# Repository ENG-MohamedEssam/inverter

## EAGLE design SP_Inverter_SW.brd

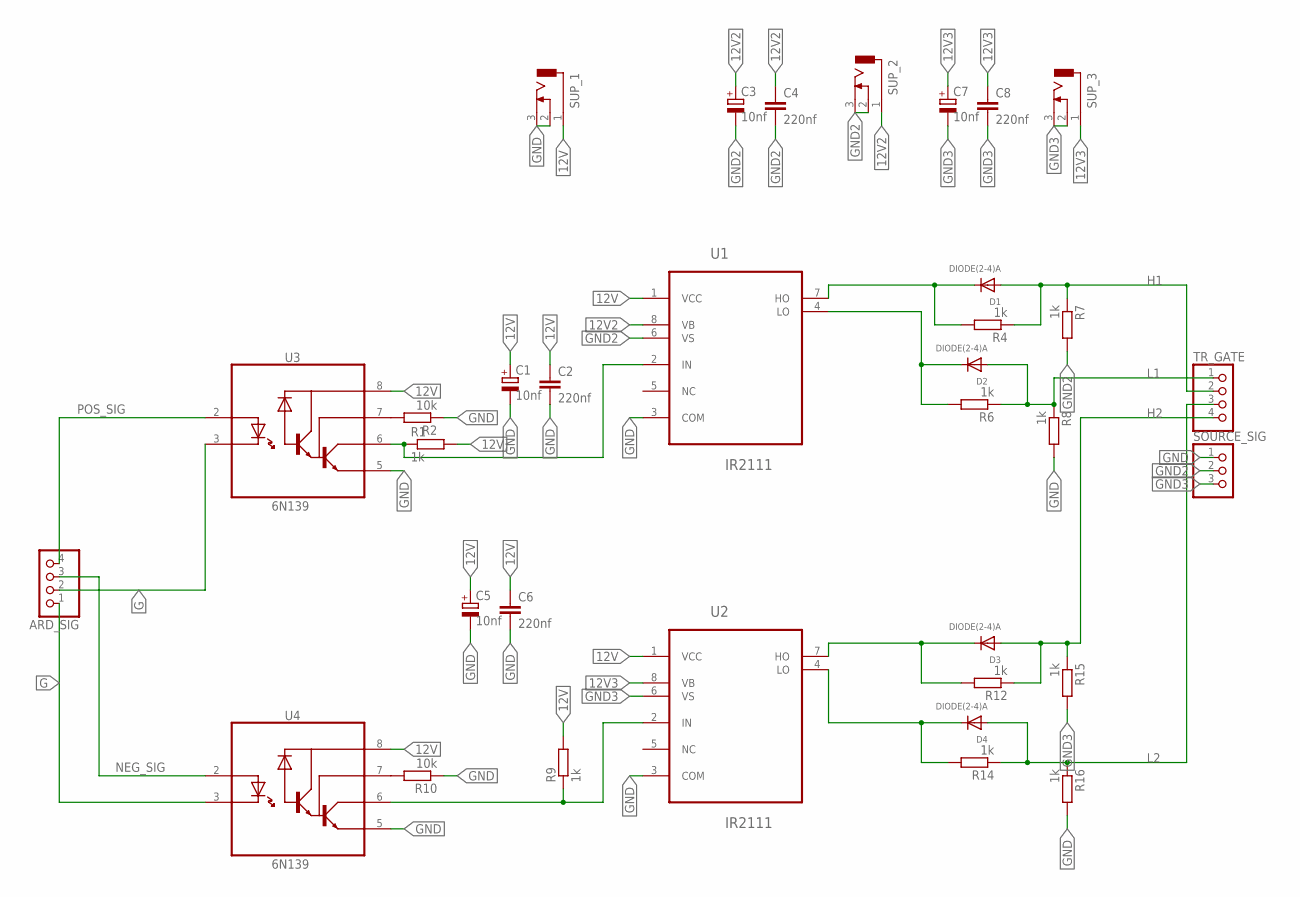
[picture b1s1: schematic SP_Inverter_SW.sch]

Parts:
ARD_SIG: PINHD-1X4; 1X04
C1, C3, C5, C7: 10nf; E3,5-8
C2, C4, C6, C8: 220nf; C025-025X050
D1, D2, D3, D4: DIODE(2-4)A; DO35-10
R1, R4, R6, R7, R8, R9, R12, R14, R15, R16: 1k; 0204/7
R2, R10: 10k; 0204/7
SOURCE_SIG: source_Sig; 1X03
SUP_1, SUP_2, SUP_3: CON_JACK; DCJ0303
TR_GATE: PINHD-1X4; 1X04
U1, U2: IR2111; DIP254P762X533-8
U3, U4: 6N139; DIP762W50P254L977H451Q8

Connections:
12V: C1.+, C2.1, C5.+, C6.1, R1.2, R9.2, SUP_1.1, U1.1 (VCC), U2.1 (VCC), U3.8 (VCC), U4.8 (VCC)
12V2: C3.+, C4.1, SUP_2.1, U1.8 (VB)
12V3: C7.+, C8.1, SUP_3.1, U2.8 (VB)
G: ARD_SIG.1, ARD_SIG.2, U3.3 (C), U4.3 (C)
GND: C1.-, C2.2, C5.-, C6.2, R2.1, R8.2, R10.1, R16.2, SOURCE_SIG.1, SUP_1.2, SUP_1.3, U1.3 (COM), U2.3 (COM), U3.5 (GND), U4.5 (GND)
GND2: C3.-, C4.2, R7.2, SOURCE_SIG.2, SUP_2.2, SUP_2.3, U1.6 (VS)
GND3: C7.-, C8.2, R15.2, SOURCE_SIG.3, SUP_3.2, SUP_3.3, U2.6 (VS)
H1: D1.A, R4.1, R7.1, TR_GATE.2
H2: D3.A, R12.1, R15.1, TR_GATE.4
L1: D2.A, R6.1, R8.1, TR_GATE.1
L2: D4.A, R14.1, R16.1, TR_GATE.3
unnamed: D1.C, R4.2, U1.7 (HO)
unnamed: D2.C, R6.2, U1.4 (LO)
unnamed: R9.1, U2.2 (IN), U4.6 (VO)
unnamed: D3.C, R12.2, U2.7 (HO)
unnamed: R2.2, U3.7 (VB)
unnamed: R1.1, U1.2 (IN), U3.6 (VO)
unnamed: R10.2, U4.7 (VB)
unnamed: D4.C, R14.2, U2.4 (LO)
NEG_SIG: ARD_SIG.3, U4.2 (A)
POS_SIG: ARD_SIG.4, U3.2 (A)

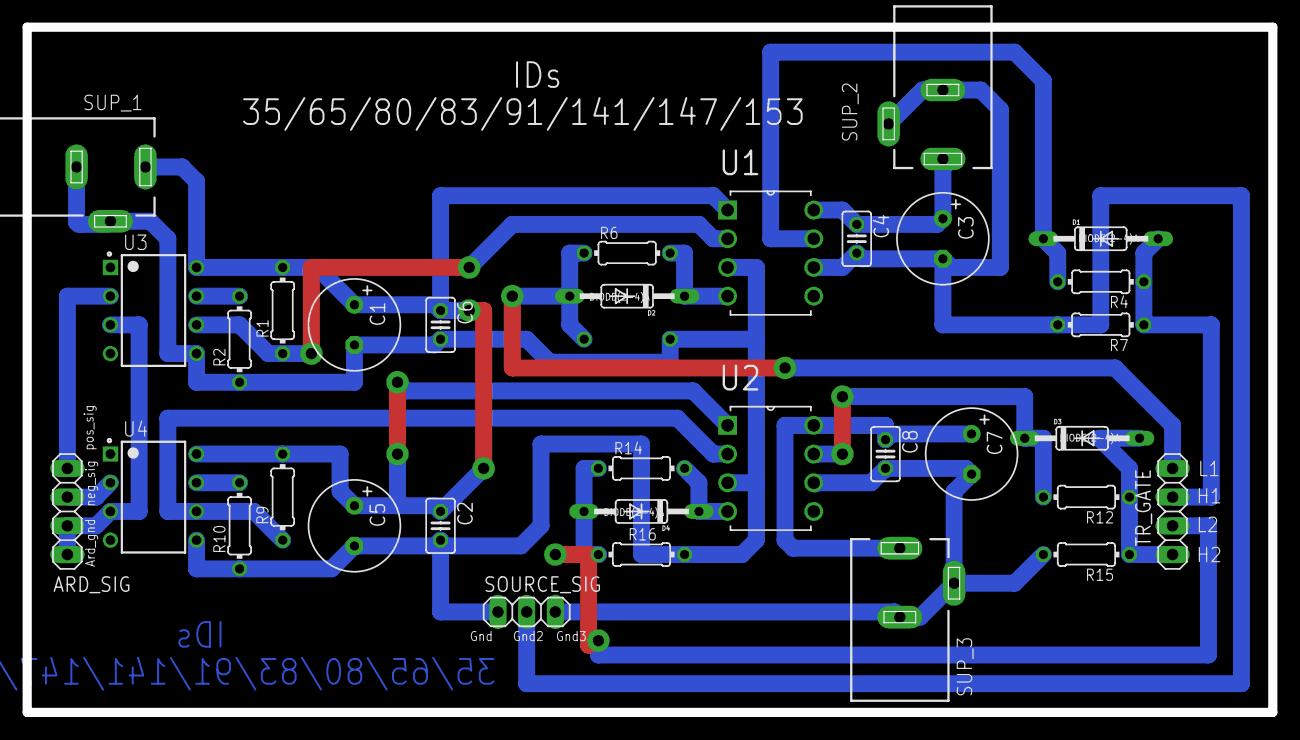
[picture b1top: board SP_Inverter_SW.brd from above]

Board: 2 copper layers, 110.2 x 60.6 mm, 34 parts (1 on the bottom side), 21 nets.

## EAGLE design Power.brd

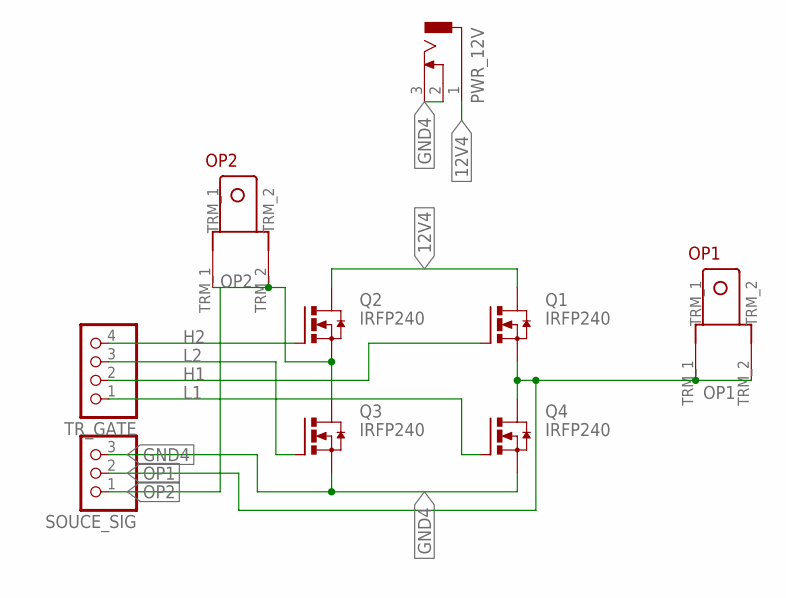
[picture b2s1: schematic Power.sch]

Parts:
OP1, OP2: TERMINAL_EDITED
PWR_12V: CON_JACK; DCJ0303
Q1, Q2, Q3, Q4: IRFP240; TO247BV
SOUCE_SIG: PINHD-1X3; 1X03
TR_GATE: PINHD-1X4; 1X04

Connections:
12V4: PWR_12V.1, Q1.D, Q2.D
GND4: PWR_12V.2, PWR_12V.3, Q3.S, Q4.S, SOUCE_SIG.3
H1: Q1.G, TR_GATE.2
H2: Q2.G, TR_GATE.4
L1: Q4.G, TR_GATE.1
L2: Q3.G, TR_GATE.3
OP1: OP1.TRM_1, OP1.TRM_2, Q1.S, Q4.D, SOUCE_SIG.2
OP2: OP2.TRM_1, OP2.TRM_2, Q2.S, Q3.D, SOUCE_SIG.1

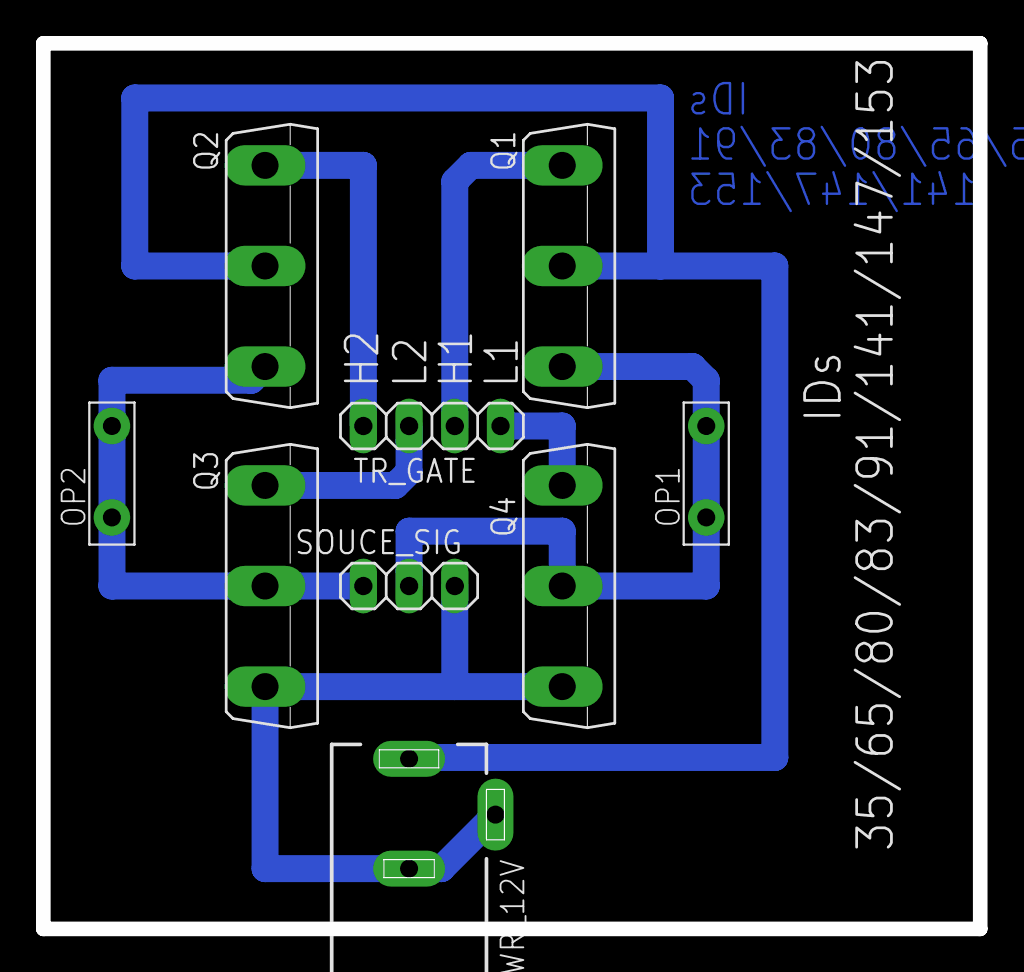
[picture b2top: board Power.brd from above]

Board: 2 copper layers, 52.0 x 49.2 mm, 9 parts (0 on the bottom side), 8 nets.
